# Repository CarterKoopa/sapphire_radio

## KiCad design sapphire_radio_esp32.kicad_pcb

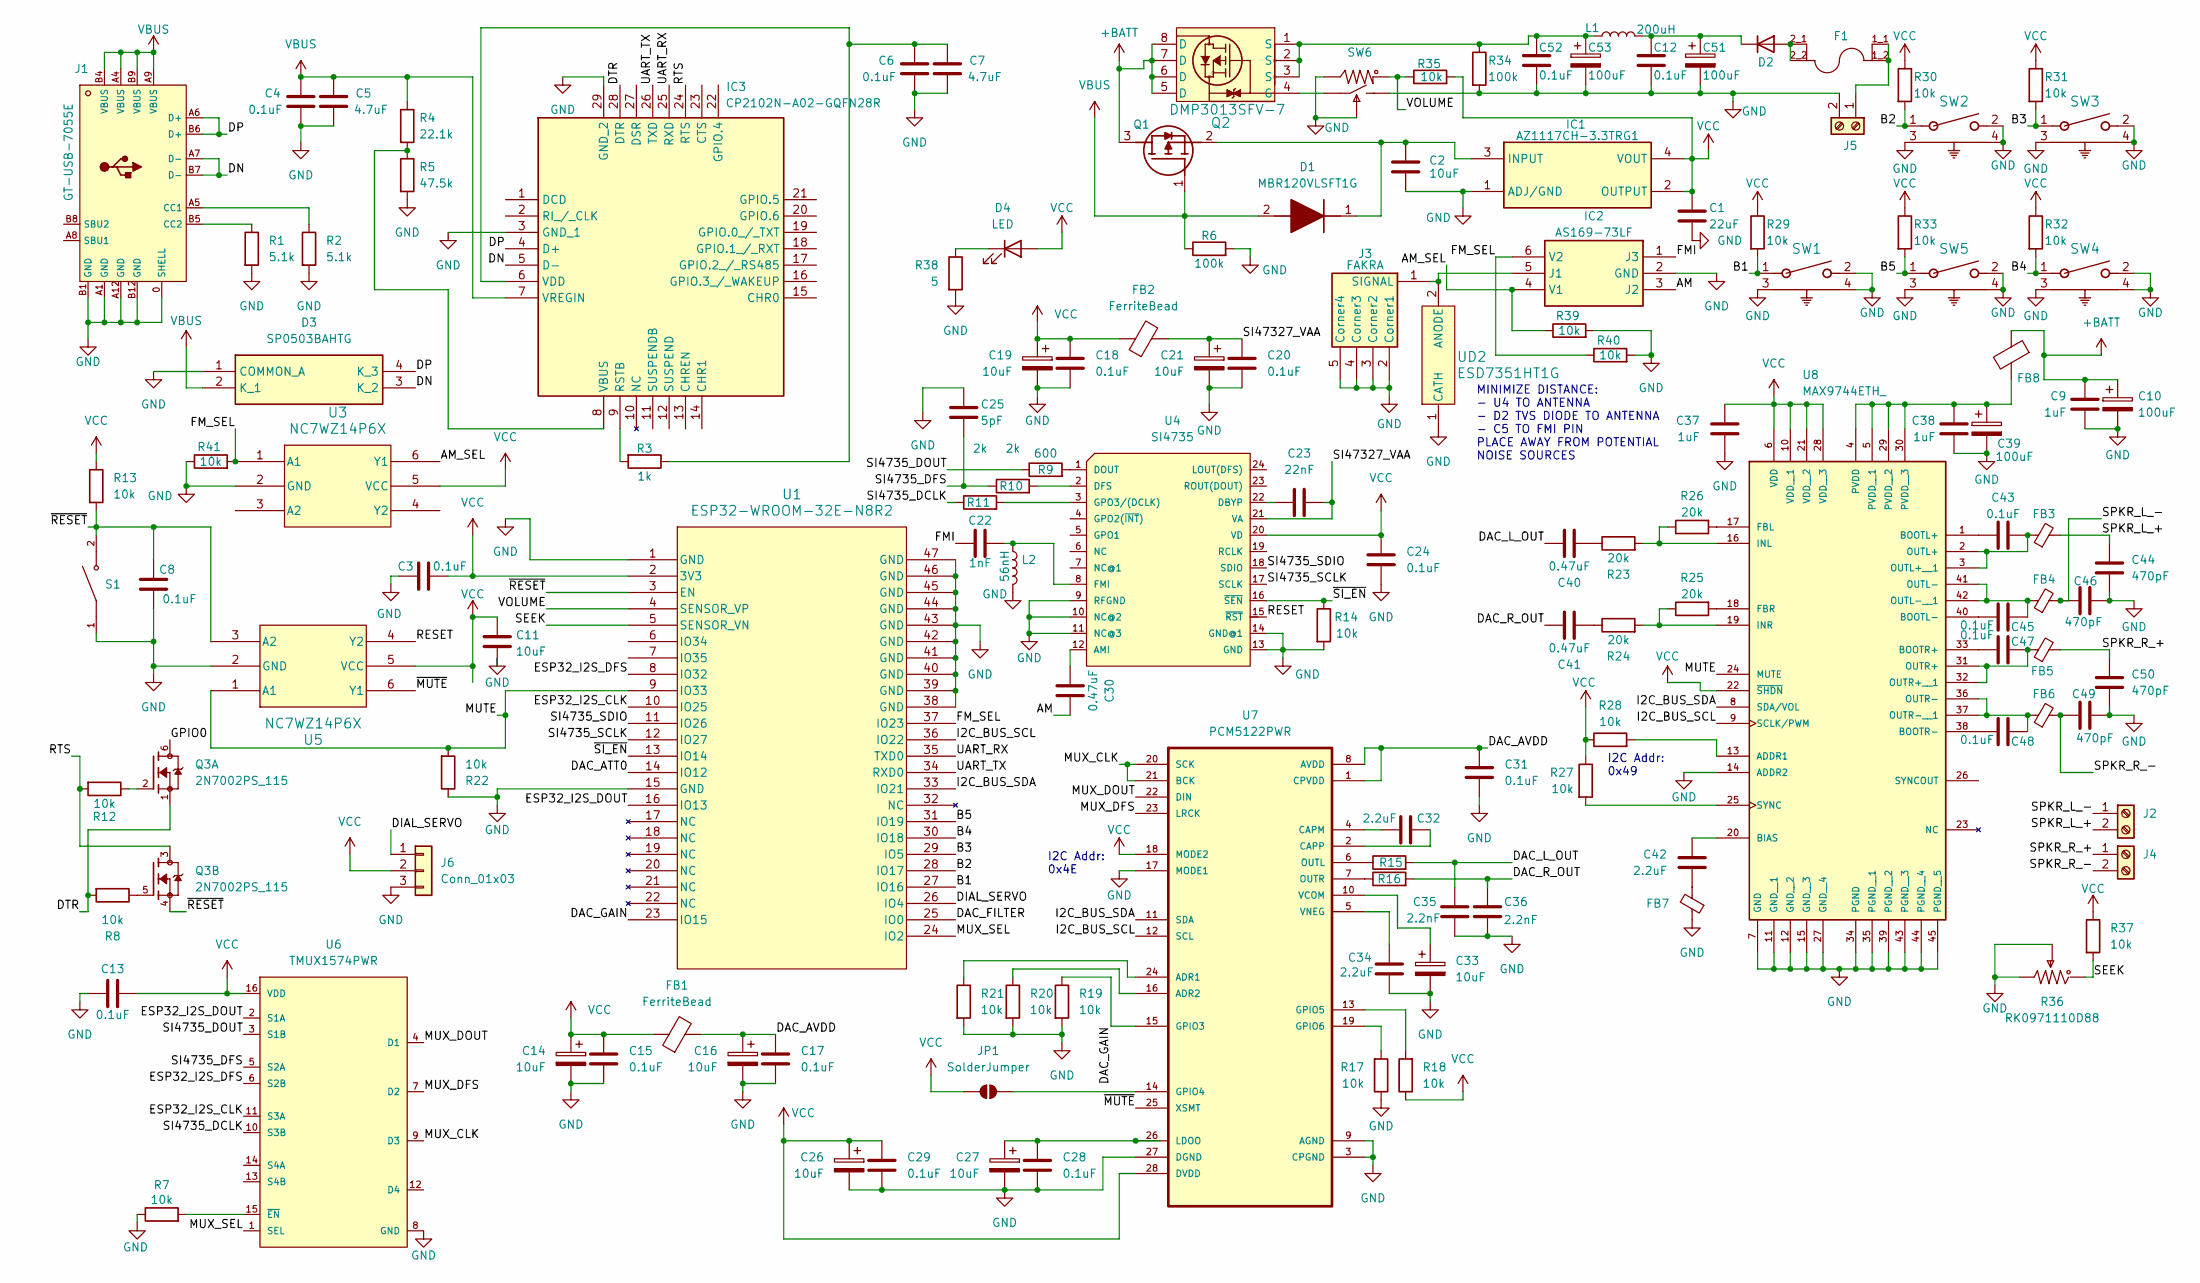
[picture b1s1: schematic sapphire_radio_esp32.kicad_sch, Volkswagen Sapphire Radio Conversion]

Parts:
C1: 22uF; C_0603_1608Metric
C2, C11: 10uF; C_0603_1608Metric
C3, C4, C6, C8, C12, C13, C43, C45, C47, C48, C52: 0.1uF; C_0603_1608Metric
C5, C7: 4.7uF; C_0603_1608Metric
C9, C37, C38: 1uF; C_0603_1608Metric
C10, C39: 100uF; WCAP-ASLI_6.3X7.7_DXL_; MPN 865080545012; DigikeyPN 732-8511-1-ND
C14, C16, C19, C21, C26, C27, C33: 10uF; CP_Elec_4x5.4; MPN 865080340001; DigikeyPN 732-8411-1-ND
C15, C17, C18, C20, C28, C29, C31: 0.1uF; C_0805_2012Metric; MPN CL21B104KCFNNNE; DigikeyPN 1276-6840-1-ND
C22: 1nF; C_0603_1608Metric; MPN CL10C102JB8NNNC; DigikeyPN 1276-1091-1-ND
C23: 22nF; C_0603_1608Metric; MPN C0603C223K5RACTU; DigikeyPN 399-C0603C223K5RACTUCT-ND
C24: 0.1uF; C_0603_1608Metric; MPN C0603C104K5RACTU; DigikeyPN 399-C0603C104K5RACTUCT-ND
C25: 5pF; C_0603_1608Metric
C30, C40, C41: 0.47uF; C_0603_1608Metric; MPN GRM188R71E474KA12D; DigikeyPN 490-3291-1-ND
C32, C34: 2.2uF; C_0603_1608Metric; MPN GRM188R61E225KA12D; DigikeyPN 490-10731-1-ND
C35, C36: 2.2nF; C_0603_1608Metric; MPN GCM1885C1H222FA16D; DigikeyPN 490-16421-1-ND
C42: 2.2uF; C_0603_1608Metric
C44, C46, C49, C50: 470pF; C_0603_1608Metric
C51, C53: 100uF; CAP_6.3_6.3; MPN EEE-FTH101XAP; DigikeyPN PCE5024CT-ND
D1: MBR120VLSFT1G; SODFL3616X98N; MPN MBR120VLSFT1G; DigikeyPN DMG2305UX-7DICT-ND
D2: D; TO-252-2; MPN SBRD10200; DigikeyPN 1655-SBRD10200CT-ND
D3: SP0503BAHTG; MPN SP0503BAHTG; DigikeyPN F2715CT-ND
D4: LED; JST_ZH_B2B-ZR-SM4-TF_1x02-1MP_P1.50mm_Vertical
F1: 3549-2; FUSE_3549-2; MPN 3549-2; DigikeyPN 36-3549-2-ND
FB1, FB2, FB8: FerriteBead; L_0603_1608Metric; MPN BLM18AG601SN1D; DigikeyPN 490-1014-1-ND
FB3, FB4, FB5, FB6, FB7: FerriteBead_Small; L_0805_2012Metric; MPN MPZ2012S221AT000; DigikeyPN 445-MPZ2012S221AT000CT-ND
IC1: AZ1117CH-3.3TRG1; SOT230P700X180-4N; MPN AZ1117CH-3.3TRG1; DigikeyPN AZ1117CH-3.3TRG1DICT-ND
IC2: AS169-73LF; SOT95P270X145-6N; MPN AS169-73LF; DigikeyPN 863-1002-1-ND
IC3: CP2102N-A02-GQFN28R; QFN50P700X700X80-45N; MPN CP2102N-A02-GQFN28R; DigikeyPN 336-5890-1-ND
J1: GT-USB-7055E; USB-C-SMD_GT-USB-7055E; MPN GT-USB-7055E; LCSCPN C7450622
J2, J4, J5: Screw_Terminal_01x02; PhoenixContact_MSTBA_2,5_2-G-5,08_1x02_P5.08mm_Horizontal
J3: FAKRA; 22913921; MPN 2291392-1; DigikeyPN 17-2291392-1CT-ND
J6: Conn_01x03; JST_PH_B3B-PH-SM4-TB_1x03-1MP_P2.00mm_Vertical
JP1: SolderJumper; SolderJumper-2_P1.3mm_Open_TrianglePad1.0x1.5mm
L1: 200uH; IND-SMD_L28.0-W25.0-74437529203331; MPN PFC-SE2822-221M; LCSCPN C42422422
L2: 56nH; L_0603_1608Metric; MPN LQW18AN56NJ00D; DigikeyPN 490-1177-1-ND
Q1: DMG2305UX-7; SOT96P240X115-3N; MPN DMG2305UX-7; DigikeyPN DMG2305UX-7DICT-ND
Q2: DMP3013SFV-7; POWERDI3333-8_UX_DIO; MPN DMP3013SFV-7; DigikeyPN DMP3013SFV-7DICT-ND
Q3: 2N7002PS_115; SOT65P210X110-6N; MPN 2N7002PS,115; DigikeyPN 1727-4791-1-ND
R1, R2: 5.1k; R_0603_1608Metric
R3: 1k; R_0603_1608Metric
R4: 22.1k; R_0603_1608Metric
R5: 47.5k; R_0603_1608Metric
R6, R34: 100k; R_0603_1608Metric
R7, R8, R12, R13, R14, R17, R18, R19, R20, R21, R22, R27, R28, R29, R30, R31, R32, R33, R35, R37, R39, R40, R41: 10k; R_0603_1608Metric
R9: 600; R_0603_1608Metric
R10, R11: 2k; R_0603_1608Metric
R15, R16: 470; R_0603_1608Metric
R23, R24, R25, R26: 20k; R_0603_1608Metric
R36: RK0971110D88; RES-ADJ-TH_RK097111080R; MPN RK0971110D88; DigikeyPN 4809-RK0971110D88-ND
R38: 5; R_0603_1608Metric
S1: B3U-1000P; SW_B3U-1000P; MPN B3U-1000P; DigikeyPN SW1020CT-ND
SW1, SW2, SW3, SW4, SW5: 1825027-8; SW2_1825027-C_TEC; MPN 1825027-8; DigikeyPN 450-1657-ND
SW6: RK09711110EL; RES-ADJ-TH_RK09711110EL; MPN RK09711110EL; DigikeyPN 4809-RK09711110EL-ND
U1: ESP32-WROOM-32E-N8R2; ESP32­WROOM­32E_EXP; MPN ESP32-WROOM-32E-N8R2; DigikeyPN 5407-ESP32-WROOM-32E-N8R2CT-ND
U3, U5: NC7WZ14P6X; SC70-6_ONS; MPN NC7WZ14P6X; DigikeyPN NC7WZ14P6XCT-ND
U4: SI4735; SSOP24-0.635-8.65X4MM; MPN SI4735-D60-GU; DigikeyPN 336-2140-ND
U6: TMUX1574PWR; Texas_Instruments-PW0016A-0-0-IPC_A; MPN TMUX1574PWR; DigikeyPN 296-53444-1-ND
U7: PCM5122PWR; SOP65P640X120-28N; MPN PCM5122PWR; DigikeyPN 296-35527-1-ND
U8: MAX9744ETH_; QFN50P700X700X80-45N; MPN MAX9744ETH+; DigikeyPN MAX9744ETH+-ND
UD2: ESD7351HT1G; DIO_MM3Z3V0T1G; MPN ESD7351HT1G; DigikeyPN ESD7351HT1GOSCT-ND

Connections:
+BATT: C9.1, C10.1, FB8.1, Q1.3 (D), Q2.5 (D), Q2.6 (D), Q2.7 (D), Q2.8 (D)
/AM: C30.1, IC2.3 (J2)
/AM_SEL: IC2.4 (V1), R39.1, U3.6 (Y1)
/B1: R29.2, SW1.1, U1.27 (IO16)
/B2: R30.2, SW2.1, U1.28 (IO17)
/B3: R31.2, SW3.1, U1.29 (IO5)
/B4: R32.2, SW4.1, U1.30 (IO18)
/B5: R33.2, SW5.1, U1.31 (IO19)
/DAC_ATT0: U1.14 (IO12)
/DAC_AVDD: C16.1, C17.1, C31.1, FB1.2, U7.1 (CPVDD), U7.8 (AVDD)
/DAC_FILTER: U1.25 (IO0)
/DAC_GAIN: R19.1, U1.23 (IO15), U7.15 (GPIO3)
/DAC_L_OUT: C35.1, C40.1, R15.2
/DAC_R_OUT: C36.1, C41.1, R16.2
/DIAL_SERVO: J6.1, U1.26 (IO4)
/DN: D3.3 (K_2), IC3.5 (D-), J1.A7 (D-), J1.B7 (D-)
/DP: D3.4 (K_3), IC3.4 (D+), J1.A6 (D+), J1.B6 (D+)
/DTR: IC3.28 (DTR), Q3.1, R8.2
/ESP32_I2S_CLK: U1.10 (IO25), U6.11 (S3A)
/ESP32_I2S_DFS: U1.8 (IO32), U6.6 (S2B)
/ESP32_I2S_DOUT: U1.16 (IO13), U6.2 (S1A)
/FMI: C22.1, IC2.1 (J3)
/FM_SEL: IC2.6 (V2), R40.1, R41.2, U1.37 (IO23), U3.1 (A1)
/GPIO0: Q3.6
/I2C_BUS_SCL: U1.36 (IO22), U7.12 (SCL), U8.9 (SCLK/PWM)
/I2C_BUS_SDA: U1.33 (IO21), U7.11 (SDA), U8.8 (SDA/VOL)
/MUTE: R22.2, U1.9 (IO33), U5.1 (A1), U8.24 (MUTE)
/MUX_CLK: U6.9 (D3), U7.20 (SCK), U7.21 (BCK)
/MUX_DFS: U6.7 (D2), U7.23 (LRCK)
/MUX_DOUT: U6.4 (D1), U7.22 (DIN)
/MUX_SEL: U1.24 (IO2), U6.1 (SEL)
/RESET: U4.15 (~RST), U5.4 (Y2)
/RTS: IC3.24 (RTS), Q3.3, R12.2
/SEEK: R36.1, R37.2, U1.5 (SENSOR_VN)
/SI4735_DCLK: R11.1, U6.10 (S3B)
/SI4735_DFS: C25.2, R10.1, U6.5 (S2A)
/SI4735_DOUT: R9.1, U6.3 (S1B)
/SI4735_SCLK: U1.12 (IO27), U4.17 (SCLK)
/SI4735_SDIO: U1.11 (IO26), U4.18 (SDIO)
/SI47327_VAA: C20.1, C21.1, C23.2, FB2.2, U4.21 (VA)
/SPKR_L_+: C44.1, FB3.2, J2.2
/SPKR_L_-: C46.1, FB4.2, J2.1
/SPKR_R_+: C50.1, FB5.2, J4.1
/SPKR_R_-: C49.1, FB6.2, J4.2
/UART_RX: IC3.25 (RXD), U1.35 (TXD0)
/UART_TX: IC3.26 (TXD), U1.34 (RXD0)
/VOLUME: R35.1, SW6.4, U1.4 (SENSOR_VP)
/~MUTE: U5.6 (Y1), U7.25 (XSMT)
/~RESET: C8.1, Q3.4, R13.2, S1.2, U1.3 (EN), U5.3 (A2)
/~SI_EN: R14.1, U1.13 (IO14), U4.16 (~SEN)
GND: C1.2, C2.2, C3.1, C4.2, C5.2, C6.2, C7.2, C8.2, C9.2, C10.2, C11.2, C12.2, C13.1, C14.2, C15.2, C16.2, C17.2, C18.2, C19.2, C20.2, C21.2, C24.2, C25.1, C26.2, C27.2, C28.2, C29.2, C31.2, C33.2, C34.1, C35.2, C36.2, C37.2, C38.2, C39.2, C44.2, C46.2, C49.2, C50.2, C51.2, C52.2, C53.2, D3.1 (COMMON_A), FB7.1, IC1.1 (ADJ/GND), IC2.2 (GND), IC3.3 (GND_1), IC3.29 (GND_2), J1.0 (SHELL), J1.A1 (GND), J1.A12 (GND), J1.B1 (GND), J1.B12 (GND), J3.2 (Corner1), J3.3 (Corner2), J3.4 (Corner3), J3.5 (Corner4), J5.2, J6.3, L2.2, R1.2, R2.2, R5.2, R6.2, R7.1, R14.2, R17.1, R19.2, R20.2, R21.2, R22.1, R34.2, R36.2, R36.3, R38.2, R39.2, R40.2, R41.1, S1.1, SW1.2, SW1.3, SW1.4, SW2.2, SW2.3, SW2.4, SW3.2, SW3.3, SW3.4, SW4.2, SW4.3, SW4.4, SW5.2, SW5.3, SW5.4, SW6.2, SW6.3, SW6.5, U1.1 (GND), U1.15 (GND), U1.38 (GND), U1.39 (GND), U1.40 (GND), U1.41 (GND), U1.42 (GND), U1.43 (GND), U1.44 (GND), U1.45 (GND), U1.46 (GND), U1.47 (GND), U3.2 (GND), U4.9 (RFGND), U4.10 (NC@2), U4.11 (NC@3), U4.13 (GND), U4.14 (GND@1), U5.2 (GND), U6.8 (GND), U7.3 (CPGND), U7.9 (AGND), U7.17 (MODE1), U7.27 (DGND), U8.7 (GND), U8.11 (GND__1), U8.12 (GND__2), U8.14 (ADDR2), U8.15 (GND__3), U8.27 (GND__4), U8.34 (PGND), U8.35 (PGND__1), U8.39 (PGND__2), U8.43 (PGND__3), U8.44 (PGND__4), U8.45 (PGND__5), UD2.1 (CATH)
unnamed: C40.2, R23.1
unnamed: C41.2, R24.1
unnamed: C42.2, FB7.2
unnamed: C52.1, C53.1, L1.1, Q2.1 (S), Q2.2 (S), Q2.3 (S), R34.1
unnamed: C2.1, D1.1 (K), IC1.3 (INPUT), Q1.2 (S)
unnamed: D2.2 (A), F1.2_1, F1.2_2
unnamed: C12.1, C51.1, D2.1 (K), L1.2
unnamed: D4.1 (K), R38.1
unnamed: IC2.5 (J1), J3.1 (SIGNAL), UD2.2 (ANODE)
unnamed: IC3.9 (RSTB), R3.2
unnamed: IC3.8 (VBUS), R4.2, R5.1
unnamed: C6.1, C7.1, IC3.6 (VDD), R3.1
unnamed: J1.A5 (CC1), R2.1
unnamed: J1.B5 (CC2), R1.1
unnamed: F1.1_1, F1.1_2, J5.1
unnamed: JP1.2 (B), U7.14 (GPIO4)
unnamed: Q2.4 (G), SW6.1
unnamed: Q3.2, R12.1
unnamed: Q3.5, R8.1
unnamed: C30.2, U4.12 (AMI)
unnamed: C23.1, U4.22 (DBYP)
unnamed: R10.2, U4.2 (DFS)
unnamed: R9.2, U4.1 (DOUT)
unnamed: C22.2, L2.1, U4.8 (FMI)
unnamed: R11.2, U4.3 (GPO3/(DCLK))
unnamed: R7.2, U6.15 (~EN)
unnamed: R21.1, U7.24 (ADR1)
unnamed: R20.1, U7.16 (ADR2)
unnamed: C32.1, U7.4 (CAPM)
unnamed: C32.2, U7.2 (CAPP)
unnamed: R18.2, U7.13 (GPIO5)
unnamed: R17.2, U7.19 (GPIO6)
unnamed: C27.1, C28.1, U7.26 (LDOO)
unnamed: R15.1, U7.6 (OUTL)
unnamed: R16.1, U7.7 (OUTR)
unnamed: C33.1, U7.10 (VCOM)
unnamed: C34.2, U7.5 (VNEG)
unnamed: R28.2, U8.13 (ADDR1)
unnamed: C42.1, U8.20 (BIAS)
unnamed: C43.1, U8.1 (BOOTL+)
unnamed: C45.1, U8.40 (BOOTL-)
unnamed: C47.1, U8.33 (BOOTR+)
unnamed: C48.1, U8.38 (BOOTR-)
unnamed: R26.2, U8.17 (FBL)
unnamed: R25.2, U8.18 (FBR)
unnamed: R23.2, R26.1, U8.16 (INL)
unnamed: R24.2, R25.1, U8.19 (INR)
unnamed: C43.2, FB3.1, U8.2 (OUTL+), U8.3 (OUTL+__1)
unnamed: C45.2, FB4.1, U8.41 (OUTL-), U8.42 (OUTL-__1)
unnamed: C47.2, FB5.1, U8.31 (OUTR+), U8.32 (OUTR+__1)
unnamed: C48.2, FB6.1, U8.36 (OUTR-), U8.37 (OUTR-__1)
unnamed: C38.1, C39.1, FB8.2, U8.4 (PVDD), U8.5 (PVDD__1), U8.29 (PVDD__2), U8.30 (PVDD__3)
unnamed: R27.2, U8.25 (SYNC)
VBUS: C4.1, C5.1, D1.2 (A), D3.2 (K_1), IC3.7 (VREGIN), J1.A4 (VBUS), J1.A9 (VBUS), J1.B4 (VBUS), J1.B9 (VBUS), Q1.1 (G), R4.1, R6.1
VCC: C1.1, C3.2, C11.1, C13.2, C14.1, C15.1, C18.1, C19.1, C24.1, C26.1, C29.1, C37.1, D4.2 (A), FB1.1, FB2.1, IC1.2 (OUTPUT), IC1.4 (VOUT), J6.2, JP1.1 (A), R13.1, R18.1, R27.1, R28.1, R29.1, R30.1, R31.1, R32.1, R33.1, R35.2, R37.1, U1.2 (3V3), U3.5 (VCC), U4.20 (VD), U5.5 (VCC), U6.16 (VDD), U7.18 (MODE2), U7.28 (DVDD), U8.6 (VDD), U8.10 (VDD__1), U8.21 (VDD__2), U8.22 (~SHDN), U8.28 (VDD__3)

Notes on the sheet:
MINIMIZE DISTANCE: - U4 TO ANTENNA - D2 TVS DIODE TO ANTENNA - C5 TO FMI PIN PLACE AWAY FROM POTENTIAL NOISE SOURCES
I2C Addr: 0x4E
I2C Addr: 0x49

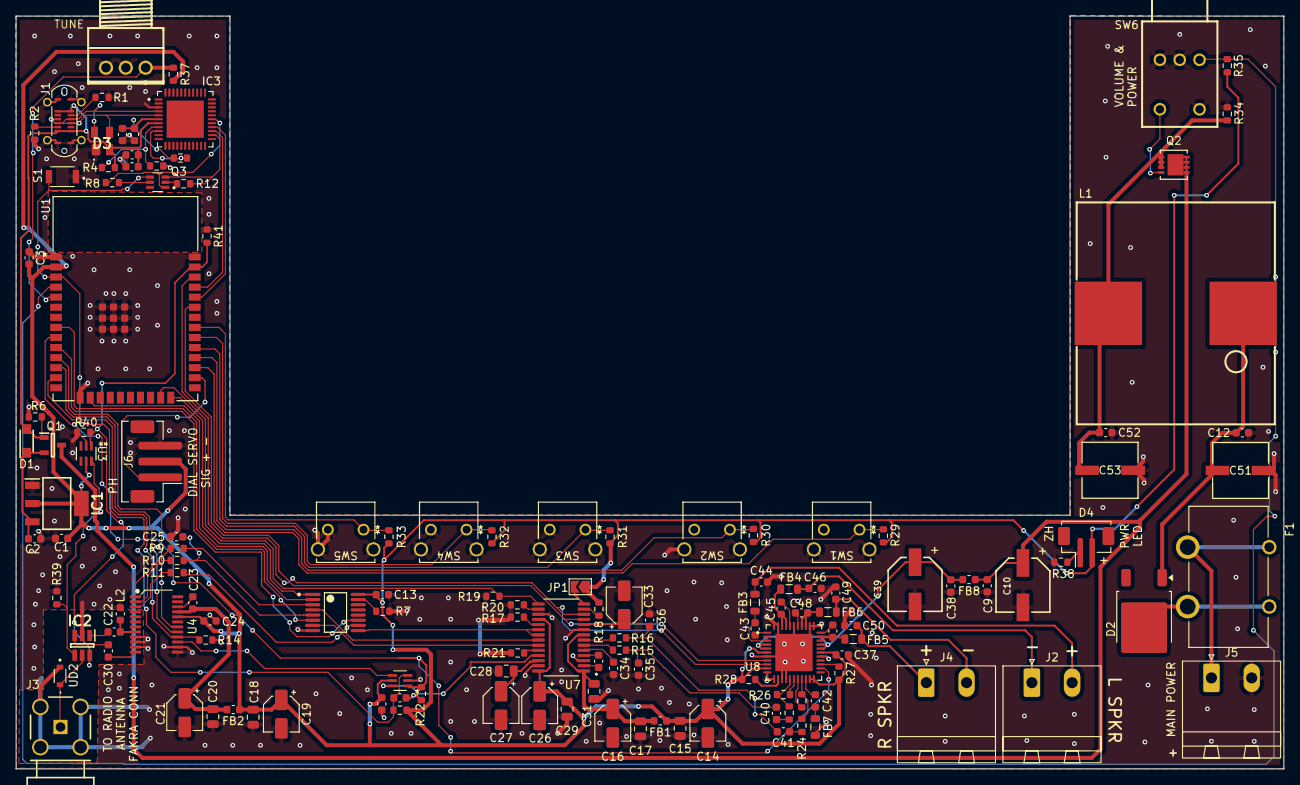
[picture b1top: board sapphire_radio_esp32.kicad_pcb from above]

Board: 2 copper layers, 160.0 x 95.0 mm, 137 parts (0 on the bottom side), 103 nets.

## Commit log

2026-03-28 Initial schematic commit
2026-03-28 Add KiCad gitignore template
2026-03-28 Add README
2026-03-28 Add fuse holder
2026-04-13 Add power filtering and pots
2026-04-15 Add board first pass; move ESP32 GPIO to allow easier routing
2026-04-23 Final WROOM revision
2026-04-24 Move fakra to board edge; move associated parts; silkscreen
